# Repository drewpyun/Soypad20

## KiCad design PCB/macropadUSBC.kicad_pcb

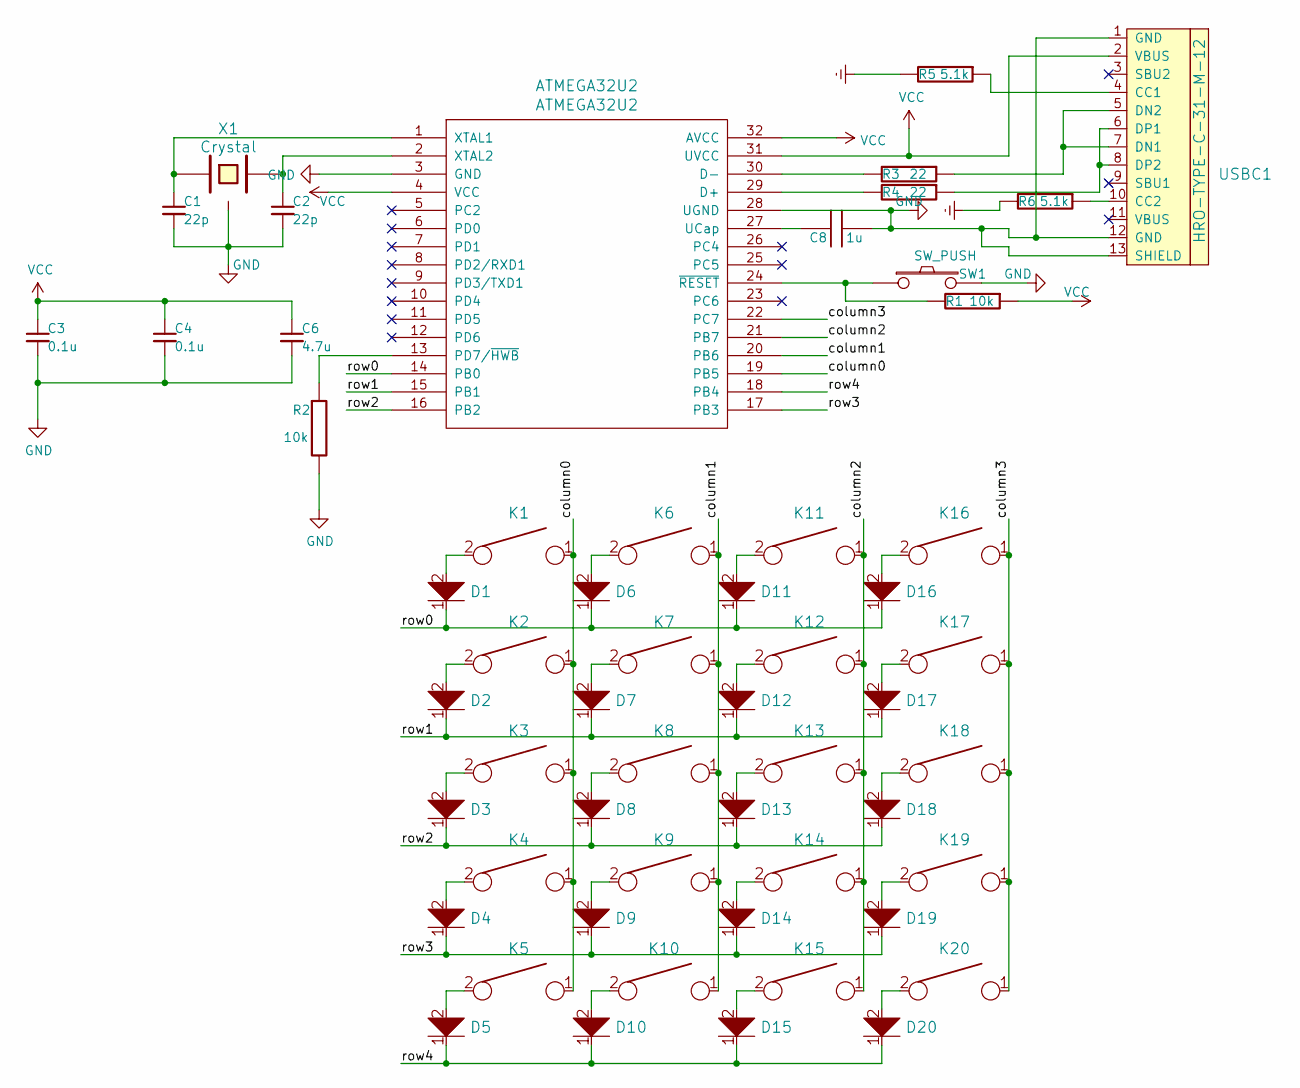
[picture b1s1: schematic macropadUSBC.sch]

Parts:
ATMEGA32U2: ATMEGA32U2; QFP32_reflow
C1, C2: 22p; C_0805_2012Metric_Pad1.15x1.40mm_HandSolder
C3, C4: 0.1u; C_0805_2012Metric_Pad1.15x1.40mm_HandSolder
C6: 4.7u; C_0805_2012Metric_Pad1.15x1.40mm_HandSolder
C8: 1u; C_0805_2012Metric_Pad1.15x1.40mm_HandSolder
D1, D2, D3, D4, D5, D6, D7, D8, D9, D10, D11, D12, D13, D14, D15, D16, D17, D18, D19, D20: D; D_SOD123_axial
K1, K2, K3, K4, K5, K6, K7, K8, K9, K10, K11, K12, K13, K14, K15, K16, K17, K18, K19, K20: KEYSW; Mx_Alps_100
R1, R2: 10k; R_0805_2012Metric_Pad1.15x1.40mm_HandSolder
R3, R4: 22; R_0805_2012Metric_Pad1.15x1.40mm_HandSolder
R5, R6: 5.1k
SW1: SW_PUSH; SW_SPST_TL3342
USBC1: HRO-TYPE-C-31-M-12
X1: Crystal; FA-238

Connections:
/column0: ATMEGA32U2.19 (PB5), K1.1, K2.1, K3.1, K4.1, K5.1; also elsewhere on the board
/column1: ATMEGA32U2.20 (PB6), K6.1, K7.1, K8.1, K9.1, K10.1; also elsewhere on the board
/column2: ATMEGA32U2.21 (PB7), K11.1, K12.1, K13.1, K14.1, K15.1; also elsewhere on the board
/column3: ATMEGA32U2.22 (PC7), K16.1, K17.1, K18.1, K19.1, K20.1; also elsewhere on the board
/row0: ATMEGA32U2.14 (PB0), D1.1, D6.1, D11.1, D16.1; also elsewhere on the board
/row1: ATMEGA32U2.15 (PB1), D2.1, D7.1, D12.1, D17.1; also elsewhere on the board
/row2: ATMEGA32U2.16 (PB2), D3.1, D8.1, D13.1, D18.1; also elsewhere on the board
/row3: ATMEGA32U2.17 (PB3), D4.1, D9.1, D14.1, D19.1; also elsewhere on the board
/row4: ATMEGA32U2.18 (PB4), D5.1, D10.1, D15.1, D20.1; also elsewhere on the board
GND: ATMEGA32U2.3 (GND), ATMEGA32U2.28 (UGND), C1.2, C2.2, C3.2, C4.2, C6.2, C8.1, R2.2, SW1.2, USBC1.1 (GND), USBC1.12 (GND), USBC1.13 (SHIELD), X1.3, X1.4; also elsewhere on the board
unnamed 10: ATMEGA32U2.1 (XTAL1), C1.1, X1.1; also elsewhere on the board
unnamed 11: ATMEGA32U2.2 (XTAL2), C2.1, X1.2; also elsewhere on the board
unnamed 12: ATMEGA32U2.27 (UCap), C8.2; also elsewhere on the board
unnamed: D1.2, K1.2
unnamed: D2.2, K2.2
unnamed: D3.2, K3.2
unnamed: D4.2, K4.2
unnamed: D5.2, K5.2
unnamed: D6.2, K6.2
unnamed: D7.2, K7.2
unnamed: D8.2, K8.2
unnamed: D9.2, K9.2
unnamed: D10.2, K10.2
unnamed: D11.2, K11.2
unnamed: D12.2, K12.2
unnamed: D13.2, K13.2
unnamed: D14.2, K14.2
unnamed: D15.2, K15.2
unnamed: D16.2, K16.2
unnamed: D17.2, K17.2
unnamed: D18.2, K18.2
unnamed: D19.2, K19.2
unnamed: D20.2, K20.2
unnamed 33: ATMEGA32U2.24 (~RESET), R1.2, SW1.1; also elsewhere on the board
unnamed 34: ATMEGA32U2.13 (PD7/~HWB), R2.1; also elsewhere on the board
unnamed 35: R3.1, USBC1.5 (DN2), USBC1.7 (DN1); also elsewhere on the board
unnamed 36: ATMEGA32U2.30 (D-), R3.2; also elsewhere on the board
unnamed 37: R4.1, USBC1.6 (DP1), USBC1.8 (DP2); also elsewhere on the board
unnamed 38: ATMEGA32U2.29 (D+), R4.2; also elsewhere on the board
unnamed: R5.1, USBC1.4 (CC1)
unnamed: R5.2, R6.2
unnamed: R6.1, USBC1.10 (CC2)
VCC: ATMEGA32U2.4 (VCC), ATMEGA32U2.31 (UVCC), ATMEGA32U2.32 (AVCC), C3.1, C4.1, C6.1, R1.1, USBC1.2 (VBUS); also elsewhere on the board

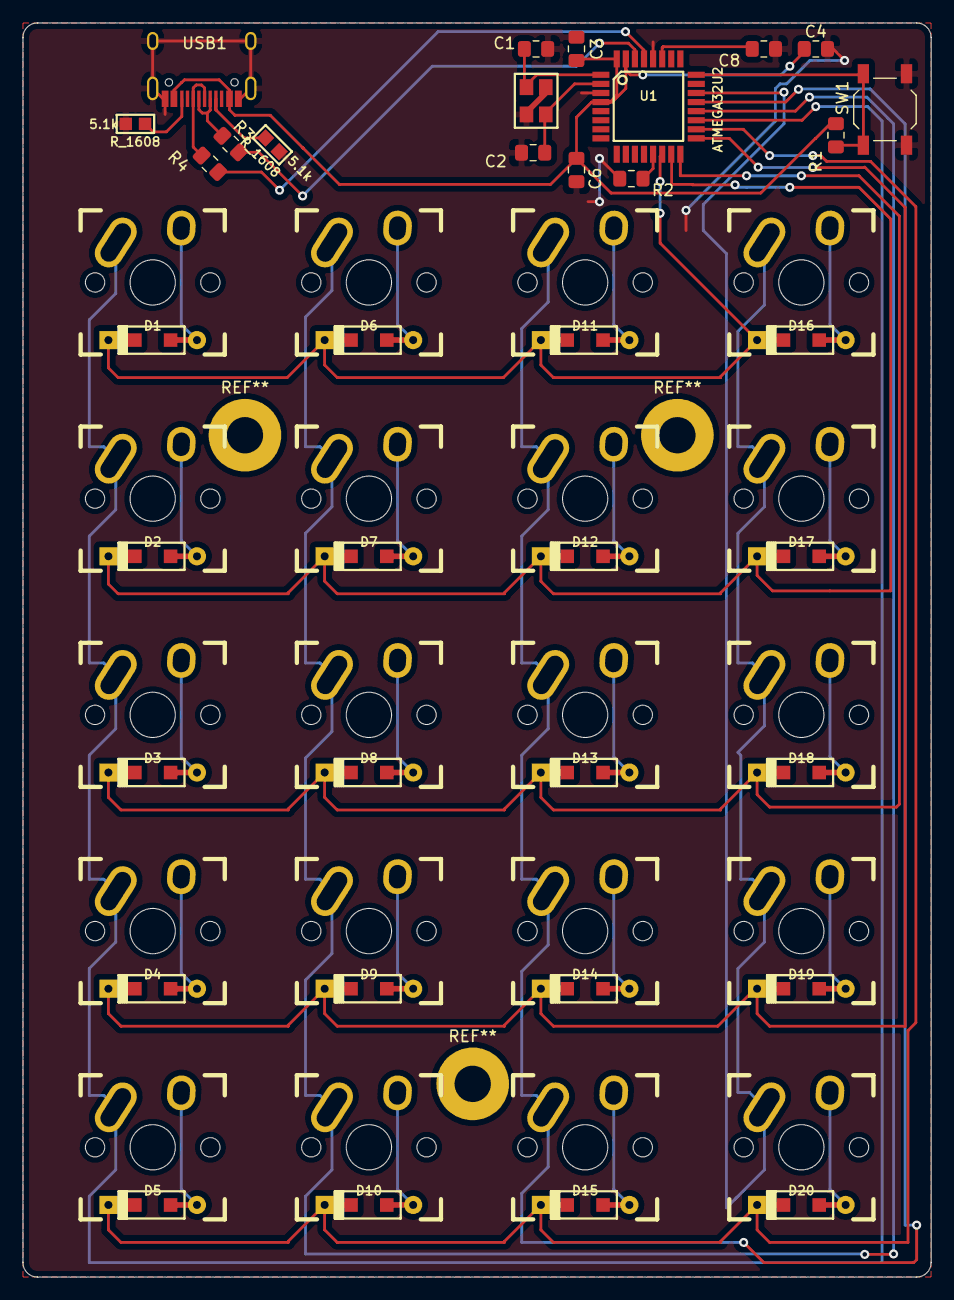
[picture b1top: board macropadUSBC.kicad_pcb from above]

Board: 2 copper layers, 80.0 x 110.5 mm, 56 parts (0 on the bottom side), 40 nets.

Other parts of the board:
R_1608, R_1608#2: 5.1k; R_1608
U1: ATMEGA32U2; QFP32_reflow
USB1: HRO-31-M-12; HRO-TYPE-C-31-M-12

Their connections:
/column0: U1.19; also elsewhere on the board
/column1: U1.20; also elsewhere on the board
/column2: U1.21; also elsewhere on the board
/column3: U1.22; also elsewhere on the board
/row0: U1.14; also elsewhere on the board
/row1: U1.15; also elsewhere on the board
/row2: U1.16; also elsewhere on the board
/row3: U1.17; also elsewhere on the board
/row4: U1.18; also elsewhere on the board
GND: R_1608.2, R_1608#2.2, U1.3, U1.28, USB1.1, USB1.12, USB1.13; also elsewhere on the board
unnamed 10: U1.1; also elsewhere on the board
unnamed 11: U1.2; also elsewhere on the board
unnamed 12: U1.27; also elsewhere on the board
unnamed 33: U1.24; also elsewhere on the board
unnamed 34: U1.13; also elsewhere on the board
unnamed 35: USB1.5, USB1.7; also elsewhere on the board
unnamed 36: U1.30; also elsewhere on the board
unnamed 37: USB1.6, USB1.8; also elsewhere on the board
unnamed 38: U1.29; also elsewhere on the board
VCC: U1.4, U1.31, U1.32, USB1.2, USB1.11; also elsewhere on the board

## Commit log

2020-07-26 Uploaded files
